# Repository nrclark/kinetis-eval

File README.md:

This repo will contain the KiCAD design files for a Kinetis KL16 eval board.
The target part is the MKL16Z64VLH4.

Status
------

At present, the schematic and PCB have both been designed. Fabrication
will be the next step.

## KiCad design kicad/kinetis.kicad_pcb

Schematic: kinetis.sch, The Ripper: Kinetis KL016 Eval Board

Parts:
C1, C2, C3, C6, C7, C8, C9, C11, C12, C13, C14, C17, C18, C19, C20: 0.1uF; SM_0603; Manufacturer PN CL10B104KO8NNNC
C4, C5, C10: 22uF; SM_1206; Manufacturer PN CC1206MKX5R7BB226
C15, C16: 27pF; SM_0603; Manufacturer PN CL10C270JB8NNNC
D1: Red; D_0805; Manufacturer PN LH R974-LP-1
D2, D3, D4, D5: 400mV@0.5A; SOD_123F; Manufacturer PN MBR120VLSFT3G
D6, D7, D8, D9: Green; D_0805; Manufacturer PN LG R971-KN-1
F1: 500mA PTC; SM_1812; Manufacturer PN 0ZCG0050FF2C
J1: FTDI_Connector; Header_0.1in_1x6; Manufacturer PN PRPC006SAAN-RC
J2, J4, J6, J7: CONN_01X16; Header_0.1in_1x16; Manufacturer PN PRPC016SAAN-RC
J3: USB_Micro_B; 10118193-0001LF_noslots; Manufacturer PN 10118193-0001LF
J5: JLink_SWD_20pin; Header_Shrouded_0.1in_2x10; Manufacturer PN 3020-20-0100-00
M1, M2, M3, M4: #4-40 Mounting Hole; 4_40_Hole; Manufacturer PN (none)
R1, R7, R15, R16, R28: 10k; SM_0805; Manufacturer PN RC0805FR-0710KL
R2, R3, R4: 200; SM_0805; Manufacturer PN RC0805FR-07200RL
R5, R27: 120; SM_0805; Manufacturer PN RC0805FR-07120RL
R6, R8, R10, R11, R12, R19, R20, R21, R22, R23, R24: 0.1; SM_0805; Manufacturer PN 73L3R10J
R9, R17, R18: DNP; SM_0805; Manufacturer PN (none)
R13, R14, R25, R26: 200; SM_0805; Manufacturer PN 73L3R10J
SW1: DPDT; GF-126-0159; Manufacturer PN GF-126-0159
SW2, SW3, SW4, SW5, SW6: SPST; PTS645_SMT; Manufacturer PN PTS645SM43SMTR92 LFS
U1: LM1117-ADJ; SOT_223_3; Manufacturer PN AZ1117EH-ADJTRG1
U2: MKL16Z64VLH4; QFP_64; Manufacturer PN MKL16Z64VLH4
Y1: 12.000 MHz; SM_HC49US; Manufacturer PN ABLS2-12.000MHZ-D4Y-T

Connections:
5V_FTDI: D3.A, J1.3 (+5V)
5V_JLink: D5.A, J5.19 (+5V)
5V_USB: D4.A, J3.1 (VCC), R17.1
+3.3V: C2.1, C4.1, C7.1, C8.1, C10.1, C11.1, C12.1, C13.1, C14.1, C17.1, C18.1, J2.3, J2.13, J2.14, J4.14, J5.1 (VTref), J7.16, R5.1, R8.2, R28.1, SW2.1, SW2.2, SW3.1, SW3.2, SW4.1, SW4.2, SW5.1, SW5.2, U2.3 (VDD), U2.13 (VDDA), U2.14 (VREFH), U2.30 (VDD), U2.48 (VDD)
/+4.6V: C3.1, C5.1, D1.A, D2.K, F1.1, U1.3
/EXTAL0: C15.1, U2.32 (PTA18/EXTAL0/TPM_CLKIN0/UART1_RX), Y1.1
/HEADER_A[1]: J2.1, U2.1 (PTE0/CMP0_OUT/I2C1_SDA/RTC_CLKOUT/SPI1_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)
/HEADER_A[2]: J2.2, U2.2 (PTE1/I2C1_SCL/SPI1_MISO/SPI1_MOSI/UART1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)
/HEADER_A[5]: J2.5, U2.5 (PTE16/ADC0_DP1/ADC0_SE1/SPI0_PCS0/TPM_C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)
/HEADER_A[6]: J2.6, U2.6 (PTE17/ADC0_DM1/ADC0_SE5a/LPTMR0_ALT3/SP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)
/HEADER_A[7]: J2.7, U2.7 (PTE18/ADC0_DP2/ADC0_SE2/I2C0_SDA/SPI0_M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)
/HEADER_A[8]: J2.8, U2.8 (PTE19/ADC0_DM2/ADC0_SE6a/I2C0_SCL/SPI0_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)
/HEADER_A[9]: J2.9, R11.2, U2.9 (PTE20/ADC0_DP0/ADC0_SE0/TPM1_CH0/UART0_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)
/HEADER_A[10]: J2.10, R12.2, U2.10 (PTE21/ADC0_DM0/ADC0_SE4a/TPM1_CH1/UART0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)
/HEADER_A[11]: J2.11, U2.11 (PTE22/ADC0_DP3/ADC0_SE3/TPM2_CH0/UART2_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)
/HEADER_A[12]: J2.12, U2.12 (PTE23/ADC0_DM3/ADC0_SE7a/TPM2_CH1/UART2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)
/HEADER_B[1]: J4.1, U2.17 (PTE29/CMP0_IN5/ADC0_SE4b/TPM0_CH2/TPM_C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)
/HEADER_B[2]: J4.2, U2.18 (PTE30/DAC0_OUT/ADC0_SE23/CMP0_IN4/TPM0_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)
/HEADER_B[3]: J4.3, U2.19 (PTE31/TPM0_CH4)
/HEADER_B[4]: J4.4, U2.20 (PTE24/I2C0_SCL/TPM0_CH0)
/HEADER_B[5]: J4.5, U2.21 (PTE25/I2C0_SDA/TPM0_CH1)
/HEADER_B[7]: J4.7, U2.23 (PTA1/TPM2_CH0/TSI0_CH2/UART0_RX)
/HEADER_B[8]: J4.8, U2.24 (PTA2/TPM2_CH1/TSI0_CH3/UART0_TX)
/HEADER_B[10]: J4.10, U2.26 (PTA4/I2C1_SDA/NMI_b/TPM0_CH1/TSI0_CH5)
/HEADER_B[11]: J4.11, U2.27 (PTA5/I2S0_TX_BCLK/TPM0_CH2)
/HEADER_B[12]: J4.12, R10.2, U2.28 (PTA12/I2S0_TXD0/TPM1_CH0)
/HEADER_B[13]: J4.13, R6.2, U2.29 (PTA13/I2S0_TX_FS/TPM1_CH1)
/HEADER_C[3]: J7.3, R26.2, U2.35 (PTB0/ADC0_SE8/TSI0_CH0/I2C0_SCL/LLWU_P5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)
/HEADER_C[4]: J7.4, R25.2, U2.36 (PTB1/ADC0_SE9/TSI0_CH6/I2C0_SDA/TPM1_CH1)
/HEADER_C[5]: J7.5, R24.2, U2.37 (PTB2/ADC0_SE12/TSI0_CH7/I2C0_SCL/TPM2_C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)
/HEADER_C[6]: J7.6, R23.2, U2.38 (PTB3/ADC0_SE13/TSI0_CH8/I2C0_SDA/TPM2_C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)
/HEADER_C[7]: J7.7, R22.2, U2.39 (PTB16/SPI1_MISO/SPI1_MOSI/TPM_CLKIN0/TS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)
/HEADER_C[8]: J7.8, R21.2, U2.40 (PTB17/SPI1_MISO/SPI1_MOSI/TPM_CLKIN1/TS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)
/HEADER_C[9]: J7.9, U2.41 (PTB18/I2S0_TX_BCLK/TPM2_CH0/TSI0_CH11)
/HEADER_C[10]: J7.10, U2.42 (PTB19/I2S0_TX_FS/TPM2_CH1/TSI0_CH12)
/HEADER_C[11]: J7.11, U2.43 (PTC0/ADC0_SE14/TSI0_CH13/CMP0_OUT/EXTRG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)
/HEADER_C[12]: J7.12, U2.44 (PTC1/ADC0_SE15/TSI0_CH14/I2C1_SCL/I2S0_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)
/HEADER_C[13]: J7.13, U2.45 (PTC2/ADC0_SE11/TSI0_CH15/I2C1_SDA/I2S0_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)
/HEADER_C[14]: J7.14, U2.46 (PTC3/CLKOUT/I2S0_TX_BCLK/LLWU_P7/TPM0_C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)
/HEADER_D[1]: J6.1, U2.49 (PTC4/I2S0_MCLK/LLWU_P8/SPI0_PCS0/TPM0_C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)
/HEADER_D[2]: J6.2, U2.50 (PTC5/CMP0_OUT/I2S0_RXD0/LPTMR0_ALT2/LLW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)
/HEADER_D[3]: J6.3, U2.51 (PTC6/CMP0_IN0/EXTRG_IN/I2S0_MCLK/I2S0_R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)
/HEADER_D[4]: J6.4, U2.52 (PTC7/CMP0_IN1/I2S0_RX_FS/SPI0_MISO/SPI0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)
/HEADER_D[5]: J6.5, U2.53 (PTC8/CMP0_IN2/I2C0_SCL/I2S0_MCLK/TPM0_C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)
/HEADER_D[6]: J6.6, U2.54 (PTC9/CMP0_IN3/I2C0_SDA/I2S0_RX_BCLK/TPM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)
/HEADER_D[7]: J6.7, U2.55 (PTC10/I2C1_SCL/I2S0_RX_FS)
/HEADER_D[8]: J6.8, U2.56 (PTC11/I2C1_SDA/I2S0_RXD0)
/HEADER_D[9]: J6.9, U2.57 (PTD0/SPI0_PCS0/TPM0_CH0)
/HEADER_D[10]: J6.10, U2.58 (PTD1/ADC0_SE5b/SPI0_SCK/TPM0_CH1)
/HEADER_D[11]: J6.11, U2.59 (PTD2/SPI0_MISO/SPI0_MOSI/TPM0_CH2/UART2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)
/HEADER_D[12]: J6.12, U2.60 (PTD3/SPI0_MISO/SPI0_MOSI/TPM0_CH3/UART2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)
/HEADER_D[13]: J6.13, R20.2, U2.61 (PTD4/LLWU_P14/SPI1_PCS0/TPM0_CH4/UART2_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)
/HEADER_D[14]: J6.14, R19.2, U2.62 (PTD5/ADC0_SE6b/SPI1_SCK/TPM0_CH5/UART2_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)
/HEADER_D[15]: J6.15, R14.2, U2.63 (PTD6/ADC0_SE7b/LLWU_P15/SPI1_MISO/SPI1_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)
/HEADER_D[16]: J6.16, R13.2, U2.64 (PTD7/SPI1_MISO/SPI1_MOSI/UART0_TX)
/LED[0]: C20.1, D9.A, R25.1
/LED[1]: C19.1, D8.A, R26.1
/LED[2]: C9.1, D7.A, R14.1
/LED[3]: C6.1, D6.A, R13.1
/PWR_IN: D3.K, D4.K, D5.K, SW1.C1
/SW[E]: R16.1, R23.1, SW5.3, SW5.4
/SW[N]: R7.1, R24.1, SW3.3, SW3.4
/SW[S]: R15.1, R22.1, SW4.3, SW4.4
/SW[W]: R1.1, R21.1, SW2.3, SW2.4
/XTAL0: C16.1, U2.33 (PTA19/LPTMR0_ALT1/TPM_CLKIN1/UART1_TX/X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), Y1.2
CTS_FTDI: J1.2 (CTS), R6.1
GND: C1.2, C2.2, C3.2, C4.2, C5.2, C6.2, C7.2, C8.2, C9.2, C10.2, C11.2, C12.2, C13.2, C14.2, C15.2, C16.2, C17.2, C18.2, C19.2, C20.2, D2.A, D6.K, D7.K, D8.K, D9.K, J1.1 (GND), J2.4, J2.15, J2.16, J3.5 (GND), J3.6, J4.15, J5.4 (GND), J5.6 (GND), J5.8 (GND), J5.10 (GND), J5.12 (GND), J7.15, M1.1, M2.1, M3.1, M4.1, R1.2, R2.2, R3.2, R4.2, R7.2, R9.2, R15.2, R16.2, R18.2, SW6.1, SW6.2, U2.4 (VSS), U2.15 (VREFL), U2.16 (VSSA), U2.31 (VSS), U2.47 (VSS)
JLink_Rx: J5.17 (Link_Rx), R19.1
JLink_SWCLK: J5.9 (SWCLK), U2.22 (PTA0/SWD_CLK/TPM0_CH5/TSI0_CH1)
JLink_SWDIO: J5.7 (SWDIO), U2.25 (PTA3/I2C1_SCL/SWD_DIO/TPM0_CH0/TSI0_CH4)
JLink_Tx: J5.5 (Link_Tx), R20.1
JLink_nRST: J5.15 (nRST), R27.1, R28.2, U2.34 (PTA20/RESET_b)
unnamed: C1.1, R3.1, R5.2, U1.1
unnamed: D1.K, R4.1
unnamed: F1.2, SW1.B1
unnamed: J3.2 (D-), R17.2
unnamed: J3.3 (D+), R18.1
unnamed: J3.4 (ID), R9.1
unnamed: R2.1, SW1.A1
unnamed: R8.1, U1.2, U1.TAB
unnamed: R27.2, SW6.3, SW6.4
RTS_FTDI: J1.6 (RTS), R10.1
RXD_FTDI: J1.5 (RXD), R11.1
TXD_FTDI: J1.4 (TXD), R12.1

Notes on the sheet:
Header for Segger J-Link Debugger
Header for 6-pin Sparkfun or Adafruit USB-UART cable.
USB Micro-B connector. Used for power only.

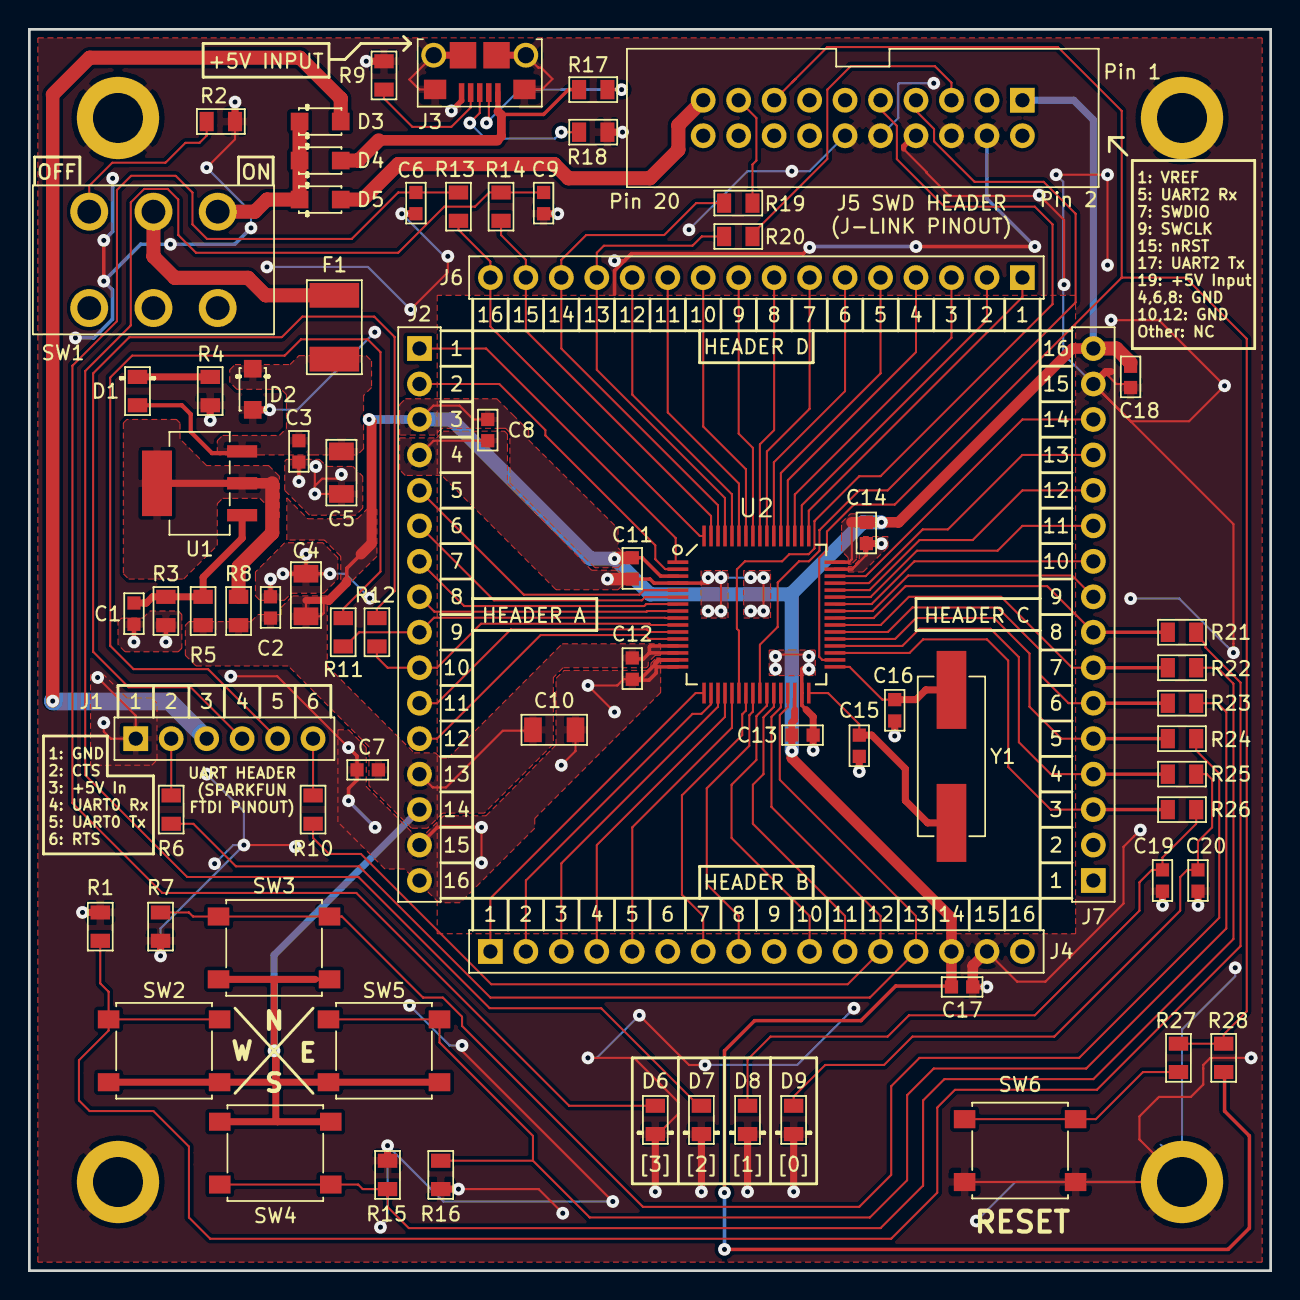
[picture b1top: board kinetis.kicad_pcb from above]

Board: 2 copper layers, 88.9 x 88.9 mm, 78 parts (0 on the bottom side), 84 nets.

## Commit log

2017-03-08 Initial commit of empty KICAD projects
2017-03-11 Work in progress.
2017-03-11 Updated schematic. Reworked Kinetis symbol. Connected LEDs.
2017-03-11 Added Kinetis reference docs
2017-03-12 Lots of changes.
    Added clock crystal and load capacitors. Added 16-pin headers to
    each side of the microcontroller. Added user pushbuttons and also
    a reset pushbutton.
2017-03-12 Schematic cleanups and part number annotations.
    This commit cleans up a lot of drafting nits, and also adds custom
    'Manufacturer' and 'Manufacturer PN' fields.
2017-03-12 Added a script for generating BOMs from KiCAD exports.
2017-03-12 Removed rescue library.
2017-03-12 Removed old cache library
2017-03-12 Cosmetic cleanups and library tweaks.
2017-03-12 Added some footprints and changed crystal footprint name.
    This commit adds a little over half of the design's required footprints,
    and also changes the name of the crystal footprint to avoid ambiguity
    with the through-hole flavors of HC49/US.
2017-03-13 Added 1x16 footprint. Added 'shield' pin to USB connector.
2017-03-13 Updated footprint library table.
2017-03-13 Added footprint for Micro-USB connector.
2017-03-13 Added footprints for 1x6 and 2x10 headers.
    This commit adds footprints for the FTDI header (1x6, 0.1") and
    the J-Link header (2x10, 0.1", shrouded). The schematic was also
    updated to match.
2017-03-13 Tweaked DPDT schematic symbol, and complete footprints.
    This commit adds the final two footprints, and also tweaks the pin
    ordering of the DPDT switch.
    The footprints should still be reviewed, but they all look good at
    a glance.
2017-03-13 Fixed schematic footprint callouts
2017-03-13 Selected custom library for all components.
2017-03-13 Added SOT-223 footprint.
2017-03-13 Renamed SOT-223 'TAB' pad.
2017-03-13 Added initial PCB spread.
2017-03-13 Added refdes fields to the fab layer on all footprints.
2017-03-13 Lots of component placement. More to go.
2017-03-13 Updated placement. More to go still.
2017-03-14 More placement and some preliminary routing
2017-03-16 Lots of layout and placement changes.
2017-03-17 Misc pin tweaks. Lots more routing.
2017-03-17 Routed some more stuff
2017-03-17 Added footprint for mounting-holes. Tweaked 2x10 footprint.
    This commit adds a footprint for 4-40 mounting holes, and also
    tightens up the 2x10 shrouded header's footprint a little bit.
2017-03-17 Added mounting holes. Moved stuff. More routing.
    This commit adds 4-40 mounting holes to the design, and shoves
    a bunch of stuff around to make room for them. It also moves
    the DPDT switch to ignore the secondary switch pole, in order to make
    some routing space.
2017-03-17 Added a few 3D models. The switch is a hack.
    This commit adds 3D models for the shrouded header and power switch,
    and also corrects the model of the 1x6 header. The power switch's 3D
    model is actually from a different switch, just squashed/mangled to
    fit into the actual footprint.
2017-03-17 More routing fun!
2017-03-17 Fixed library gaff
2017-03-17 Added lots more 3D models, including a janky USB.
    This commit adds 3D models to all components that were missing them.
    The USB connetor's model is 100% wrong, and either the model needs
    to be verified or the component needs to be replaced.
2017-03-17 Placement tweaks, 3D models, and board outline.
2017-03-19 Updated PCB layout.
2017-03-19 Reconciled +3.3V and +3V3 nets
2017-03-19 Expanded copper pours
2017-03-20 Completed analog power. Added extra 22uF cap.
    This commit adds another 22uF capacitor to the analog rail, and
    also completes the power plane pour.
2017-03-21 Completed routing. Some silkscreen work.
2017-03-21 Silkscreen work
2017-03-21 Completed silkscreen cleanup.
2017-03-22 Renamed 5V input net
2017-03-22 Back-annotated schematic from PCB.
    This commit back-annotates the schematic from the PCB, and
    includes the script that was used to do it.
2017-03-22 Added cutout to shrouded silkscreen
2017-03-22 More routing tweaks
2017-03-22 Improved the +3.3V analog section
2017-03-22 Yet more tweaks
2017-03-23 Updated USB 3-D model
2017-03-23 Re-applied annotation
2017-03-23 Tweaked outline on SOD-123 footprint
2017-03-23 Updated SOD-123 footprint. Cleaned up fab drawing.
2017-03-23 Changed USB connector. Fixed soldermask clearance settings.
    This commit changes the USB connector from an SMT-only connector
    to one with some through-hole mounting tabs. This should help to
    provide mechanical ruggedness for the board.
    This commit also fixed the soldermask clearance settings so that the
    USB connector and Kinets both have soldermask in-between the pins.
2017-03-23 Bugfix to USB 3D model. Added ground stitches.
    This commit fixes the selection of the USB connector's 3D model.
    It also adds some small ground patches over the 3.3V disruptions
    under the Kinetis.
2017-03-23 Tweaks
2017-03-24 Misc tweaks
2017-03-25 Cosmetic tweaks. Added copper thieving.
    This commit adds ground-referenced copper thieving to the top layer
    of the PCB, and also makes a whole bunch of cosmetic changes, including
    a logo on the PCB and schematic, and infoblocks for the CCA and PCB.
2017-03-25 Added silkscreen writing area to CCA title block. Added signature.
    This commit adds a couple of new virtual footprints that are used
    on the PCB.
2017-03-25 Various cosmetic tweaks
2017-03-25 Removed GND-fill pour from top side
2017-03-25 Cleaned up component-annotation script.
    This commit cleans up the early component-reannotation script
    I wrote, and turns it into a standalone utility. The script
    targets python2, which is KiCAD's scripting interface at the
    time of this writing.
2017-03-25 Updated help for annotation script.
2017-03-26 Added script for generating drill files.
2017-03-26 Added script for generating Gerber files
2017-03-26 Changed generate-drills.py to have a retval
2017-03-26 Added some more copper. Changed vias to 0.014"/0.032".
2017-03-27 Adde a shitload of copper
2017-03-27 Added a couple more stitch vias
2017-03-27 Added list of allowed holes from ExpressPCB. Tweaked hole-checker.
    This commit tweaks the hole-checker to allow comments in hole lists,
    and also adds a list to use as a reference.
2017-03-27 Updated parts to use whiteliseted hole sizes
2017-03-27 More misc cleanups
2017-03-27 Added Makefile for generating outputs
2017-03-27 Makefile updates and fixes
2017-03-27 Lots of Makefile cleanups
2017-03-27 Footprint and copper tweaks.
    This commit changes out the USB connector footprint for a tweaked
    version with thru-holes instead of slots. It also fixes a minor
    silkscreen bug in the SM_0805 package, and lengthens the CCA
    title block.
    Additionally, the GND pours on top/bottom were pulled back from the
    PCB edge by 0.020".
2017-03-27 Tweaked Makefile to include paste-top layer
2017-03-27 Sent to Seeed
2017-04-03 Fixed the manufacturer/part-numers for resistors.
    This commit changes the MFR and MFR PN for four 200-ohm resistors
    which were accidentally called out with 0.1-ohm part numbers. Oops.
2017-04-03 Cleanups and tweaks to BOM export script.
    This commit tweaks the BOM exporter so that it always generates
    .txt files (required for an automatic Digikey import at the time
    of this writing), and also fixes the line-item generator.
    Some pylint/pep8 cleanups are also included for good measure.
